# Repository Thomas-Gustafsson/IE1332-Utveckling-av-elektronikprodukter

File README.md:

# IE1332-Utveckling-av-elektronikprodukter

- "STM32.zip" innehåller mitt laborationsarbete i kursen, LAB1. Kretskortsdesign av en mikrokontroller skapat i KiCad 7.
- "Improving Energy Efficiency in Mobile Networks" är en skriftlig uppgift som tillhör momentet LIT1 där syftet är att diskutera användandet av elektronik för ett hållbart samhälle. Område att skriva om väljer man själv.

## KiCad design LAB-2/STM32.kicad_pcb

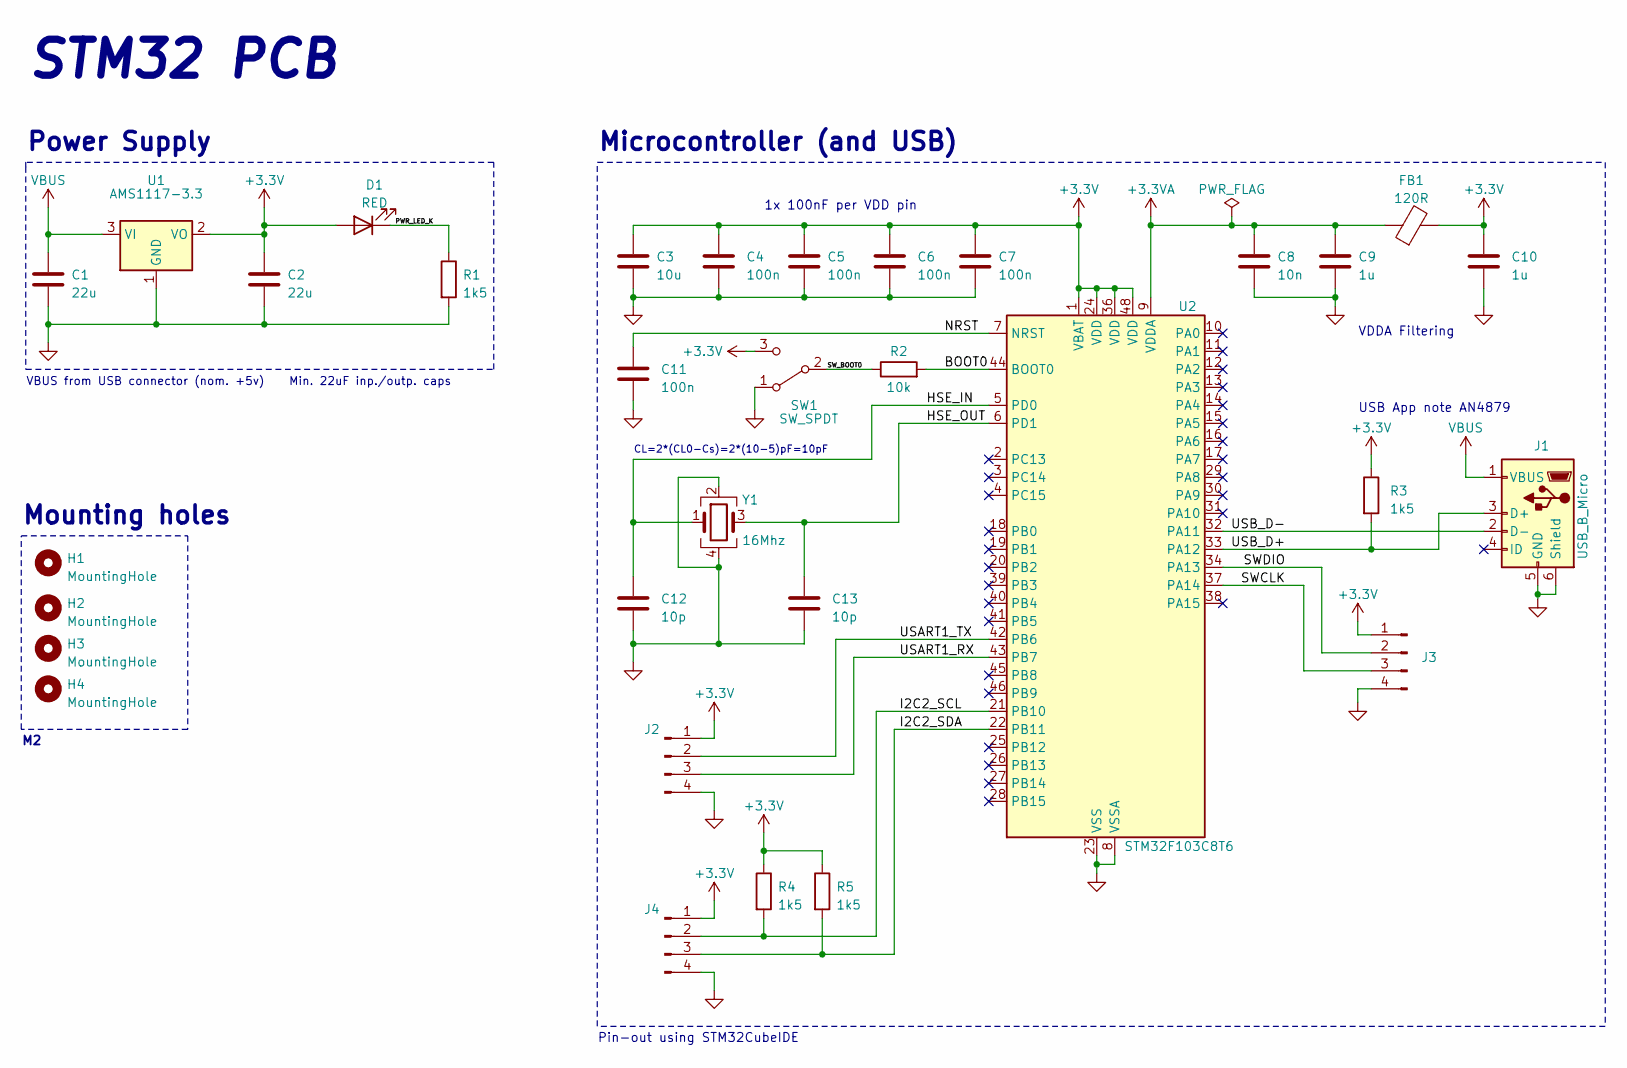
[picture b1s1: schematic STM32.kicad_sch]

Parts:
C1, C2: 22u; C_0805_2012Metric
C3: 10u; C_0805_2012Metric
C4, C5, C6, C7, C11: 100n; C_0805_2012Metric
C8: 10n; C_0805_2012Metric
C9, C10: 1u; C_0805_2012Metric
C12, C13: 10p; C_0805_2012Metric
D1: RED; LED_0805_2012Metric
FB1: 120R; L_0805_2012Metric
H1, H2, H3, H4: MountingHole; MountingHole_2.2mm_M2
J1: USB_B_Micro; USB_Micro-B_Amphenol_10104110_Horizontal
J2, J3, J4: Conn_01x04_Pin; PinHeader_1x04_P2.54mm_Vertical
R1, R3, R4, R5: 1k5; R_0805_2012Metric
R2: 10k; R_0805_2012Metric
SW1: SW_SPDT; SW_SPDT_PCM12
U1: AMS1117-3.3; SOT-223-3_TabPin2
U2: STM32F103C8T6; LQFP-48_7x7mm_P0.5mm
Y1: 16Mhz; Crystal_SMD_3225-4Pin_3.2x2.5mm

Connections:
+3.3V: C2.1, C3.1, C4.1, C5.1, C6.1, C7.1, C10.1, D1.2 (A), FB1.2, J2.1, J3.1, J4.1, R3.1, R4.1, R5.1, SW1.3 (C), U1.2 (VO), U2.1 (VBAT), U2.24 (VDD), U2.36 (VDD), U2.48 (VDD)
+3.3VA: C8.1, C9.1, FB1.1, U2.9 (VDDA)
/BOOT0: R2.2, U2.44 (BOOT0)
/HSE_IN: C12.1, U2.5 (PD0), Y1.1
/HSE_OUT: C13.1, U2.6 (PD1), Y1.3
/I2C2_SCL: J4.2, R4.2, U2.21 (PB10)
/I2C2_SDA: J4.3, R5.2, U2.22 (PB11)
/NRST: C11.1, U2.7 (NRST)
/PWR_LED_K: D1.1 (K), R1.1
/SWCLK: J3.3, U2.37 (PA14)
/SWDIO: J3.2, U2.34 (PA13)
/SW_BOOT0: R2.1, SW1.2 (B)
/USART1_RX: J2.3, U2.43 (PB7)
/USART1_TX: J2.2, U2.42 (PB6)
/USB_D+: J1.3 (D+), R3.2, U2.33 (PA12)
/USB_D-: J1.2 (D-), U2.32 (PA11)
GND: C1.2, C2.2, C3.2, C4.2, C5.2, C6.2, C7.2, C8.2, C9.2, C10.2, C11.2, C12.2, C13.2, J1.5 (GND), J1.6 (Shield), J2.4, J3.4, J4.4, R1.2, SW1.1 (A), U1.1 (GND), U2.8 (VSSA), U2.23 (VSS), U2.35 (VSS), U2.47 (VSS), Y1.2, Y1.4
VBUS: C1.1, J1.1 (VBUS), U1.3 (VI)

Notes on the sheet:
1x 100nF per VDD pin
VBUS from USB connector (nom. +5v) Min. 22uF inp./outp. caps
Pin-out using STM32CubeIDE
VDDA Filtering
CL=2*(CL0-Cs)=2*(10-5)pF=10pF
USB App note AN4879
Power Supply
STM32 PCB
Microcontroller (and USB)
Mounting holes

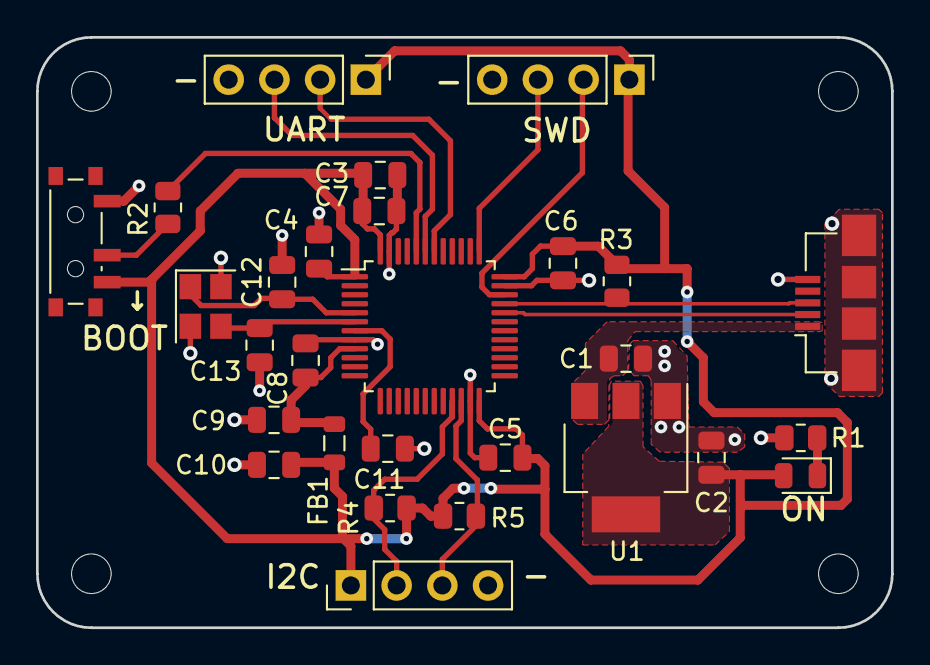
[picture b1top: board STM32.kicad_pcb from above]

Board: 2 copper layers, 47.5 x 32.8 mm, 32 parts (0 on the bottom side), 18 nets.

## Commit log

2023-04-23 Create test
